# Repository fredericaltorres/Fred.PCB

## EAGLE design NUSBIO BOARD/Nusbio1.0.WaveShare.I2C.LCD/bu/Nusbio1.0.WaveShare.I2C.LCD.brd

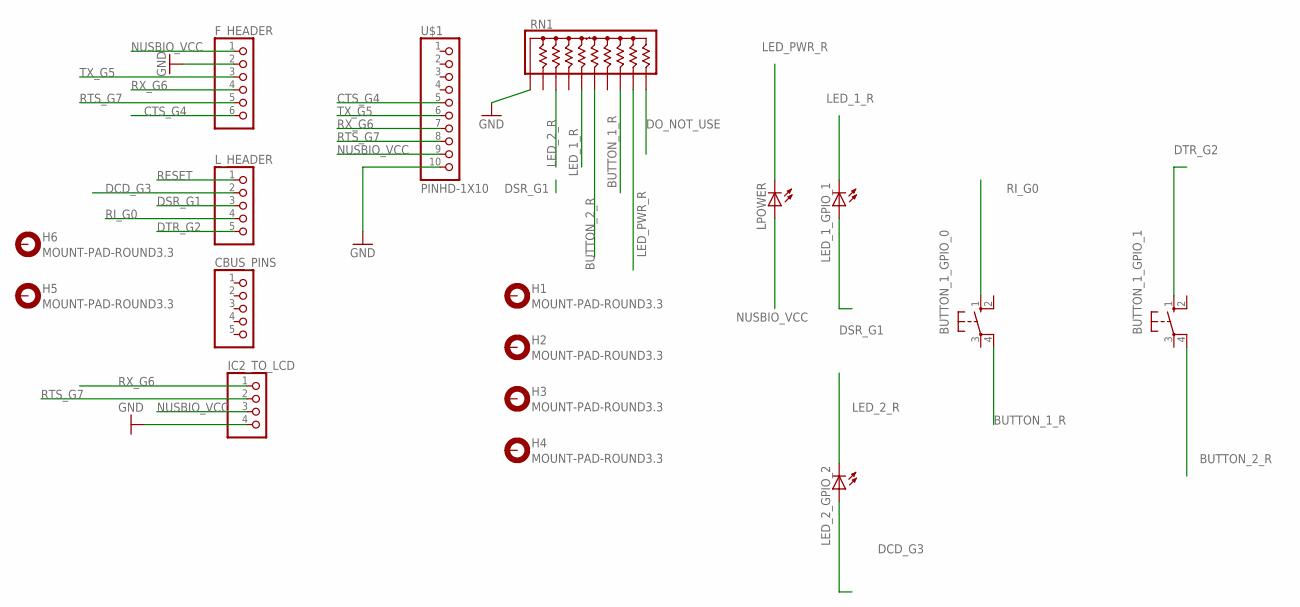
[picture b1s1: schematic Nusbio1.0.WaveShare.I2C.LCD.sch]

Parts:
BUTTON_1_GPIO_0, BUTTON_1_GPIO_1: 10-XX; B3F-10XX
CBUS_PINS: PINHD-1X5; 1X05
F_HEADER: PINHD-1X6; 1X06
H1, H2, H3, H4, H5, H6: MOUNT-PAD-ROUND3.3; 3,3-PAD
IC2_TO_LCD: PINHD-1X4; 1X04
LED_1_GPIO_1, LED_2_GPIO_2: LEDSMT1206; 1206
LPOWER: LEDSMT1206; 1206
L_HEADER: PINHD-1X5; 1X05
RN1: 4610X; SIP10
U$1: PINHD-1X10; 1X10-BIG

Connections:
BUTTON_1_R: BUTTON_1_GPIO_0.4 (P1), RN1.8
BUTTON_2_R: BUTTON_1_GPIO_1.4 (P1), RN1.6
CTS_G4: F_HEADER.6, U$1.5
DCD_G3: LED_2_GPIO_2.A, L_HEADER.2
DO_NOT_USE: RN1.10
DSR_G1: LED_1_GPIO_1.A, L_HEADER.3
DTR_G2: BUTTON_1_GPIO_1.1 (S), L_HEADER.5
GND: F_HEADER.2, IC2_TO_LCD.4, RN1.1, U$1.10
LED_1_R: LED_1_GPIO_1.C, RN1.5
LED_2_R: LED_2_GPIO_2.C, RN1.3
LED_PWR_R: LPOWER.C, RN1.9
NUSBIO_VCC: F_HEADER.1, IC2_TO_LCD.3, LPOWER.A, U$1.9
RESET: L_HEADER.1
RI_G0: BUTTON_1_GPIO_0.1 (S), L_HEADER.4
RTS_G7: F_HEADER.5, IC2_TO_LCD.2, U$1.8
RX_G6: F_HEADER.4, IC2_TO_LCD.1, U$1.7
TX_G5: F_HEADER.3, U$1.6

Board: 2 copper layers, 17 parts (0 on the bottom side), 15 nets, no tracks yet.

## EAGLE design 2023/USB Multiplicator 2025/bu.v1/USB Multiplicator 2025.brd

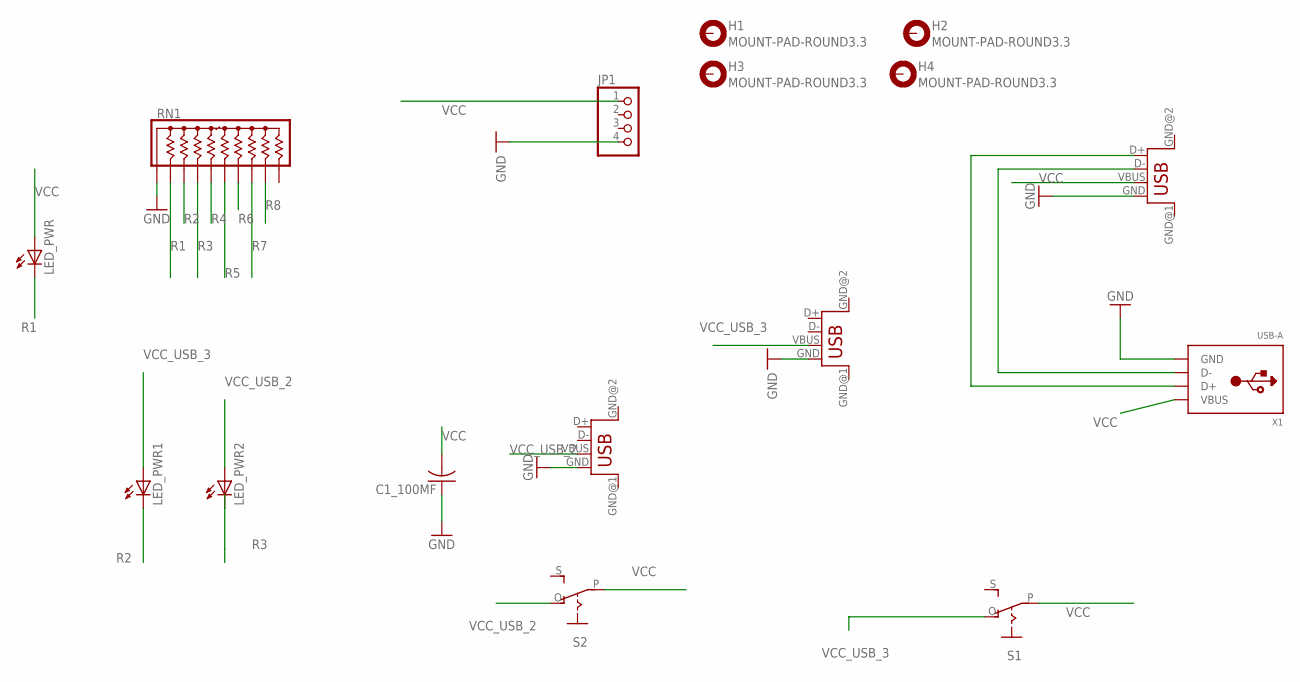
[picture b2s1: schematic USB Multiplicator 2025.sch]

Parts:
C1_100MF: C-US025-030X050; C025-030X050
H1, H2, H3, H4: MOUNT-PAD-ROUND3.3; 3,3-PAD
JP1: PINHD-1X4; 1X04
LED_PWR, LED_PWR1, LED_PWR2: LEDSMT1206; 1206
RN1: 4610X; SIP10
S1, S2: EG1218S; EG1218
USB_OUT_1, USB_OUT_2: USB; USB-FEMALE-A-PTH
USB_OUT_WITH_DATA_1: USB; USB-FEMALE-A-PTH
X1: USB-A; MOLEX_480371000

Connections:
GND: C1_100MF.1, JP1.4, RN1.1, USB_OUT_1.GND, USB_OUT_2.GND, USB_OUT_WITH_DATA_1.GND, X1.4 (GND)
unnamed: USB_OUT_WITH_DATA_1.D-, X1.2 (D-)
unnamed: USB_OUT_WITH_DATA_1.D+, X1.3 (D+)
R1: LED_PWR.C, RN1.2
R2: LED_PWR1.C, RN1.3
R3: LED_PWR2.C, RN1.4
R4: RN1.5
R5: RN1.6
R6: RN1.7
R7: RN1.8
R8: RN1.9
VCC: C1_100MF.2, JP1.1, LED_PWR.A, S1.P, S2.P, USB_OUT_WITH_DATA_1.VBUS, X1.1 (VBUS)
VCC_USB_2: LED_PWR2.A, S2.O, USB_OUT_2.VBUS
VCC_USB_3: LED_PWR1.A, S1.O, USB_OUT_1.VBUS

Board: 2 copper layers, 16 parts (0 on the bottom side), 9 nets, no tracks yet.

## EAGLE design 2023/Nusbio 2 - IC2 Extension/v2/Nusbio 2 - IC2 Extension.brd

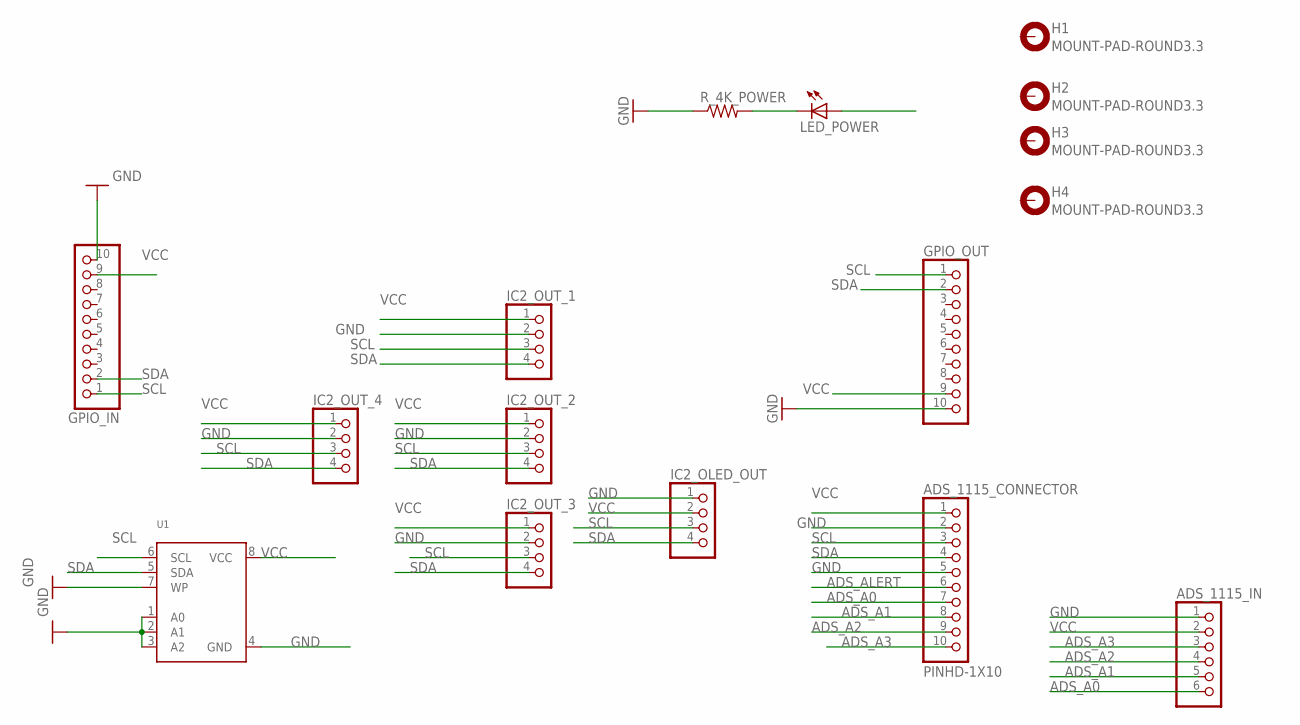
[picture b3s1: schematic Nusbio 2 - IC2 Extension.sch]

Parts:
ADS_1115_CONNECTOR: PINHD-1X10; 1X10-BIG
ADS_1115_IN: PINHD-1X6; 1X06
GPIO_IN: PINHD-1X10; 1X10-BIG
GPIO_OUT: PINHD-1X10; 1X10-BIG
H1, H2, H3, H4: MOUNT-PAD-ROUND3.3; 3,3-PAD
IC2_OLED_OUT, IC2_OUT_1, IC2_OUT_2, IC2_OUT_3, IC2_OUT_4: PINHD-1X4; 1X04
LED_POWER: LEDSMT1206; 1206
R_4K_POWER: R-US_R1206; R1206
U1: EEPROM_I2C_SOIC8_GENERIC; SOIC8_150MIL

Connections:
ADS_A0: ADS_1115_CONNECTOR.7, ADS_1115_IN.6
ADS_A1: ADS_1115_CONNECTOR.8, ADS_1115_IN.5
ADS_A2: ADS_1115_CONNECTOR.9, ADS_1115_IN.4
ADS_A3: ADS_1115_CONNECTOR.10, ADS_1115_IN.3
ADS_ALERT: ADS_1115_CONNECTOR.6
GND: ADS_1115_CONNECTOR.2, ADS_1115_CONNECTOR.5, ADS_1115_IN.1, GPIO_IN.10, GPIO_OUT.10, IC2_OLED_OUT.1, IC2_OUT_1.2, IC2_OUT_2.2, IC2_OUT_3.2, IC2_OUT_4.2, R_4K_POWER.1, U1.1 (A0), U1.2 (A1), U1.3 (A2), U1.4 (GND), U1.7 (WP)
unnamed: LED_POWER.C, R_4K_POWER.2
SCL: ADS_1115_CONNECTOR.3, GPIO_IN.1, GPIO_OUT.1, IC2_OLED_OUT.3, IC2_OUT_1.3, IC2_OUT_2.3, IC2_OUT_3.3, IC2_OUT_4.3, U1.6 (SCL)
SDA: ADS_1115_CONNECTOR.4, GPIO_IN.2, GPIO_OUT.2, IC2_OLED_OUT.4, IC2_OUT_1.4, IC2_OUT_2.4, IC2_OUT_3.4, IC2_OUT_4.4, U1.5 (SDA)
VCC: ADS_1115_CONNECTOR.1, ADS_1115_IN.2, GPIO_IN.9, GPIO_OUT.9, IC2_OLED_OUT.2, IC2_OUT_1.1, IC2_OUT_2.1, IC2_OUT_3.1, IC2_OUT_4.1, LED_POWER.A, U1.8 (VCC)

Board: 2 copper layers, 16 parts (0 on the bottom side), 9 nets, no tracks yet.

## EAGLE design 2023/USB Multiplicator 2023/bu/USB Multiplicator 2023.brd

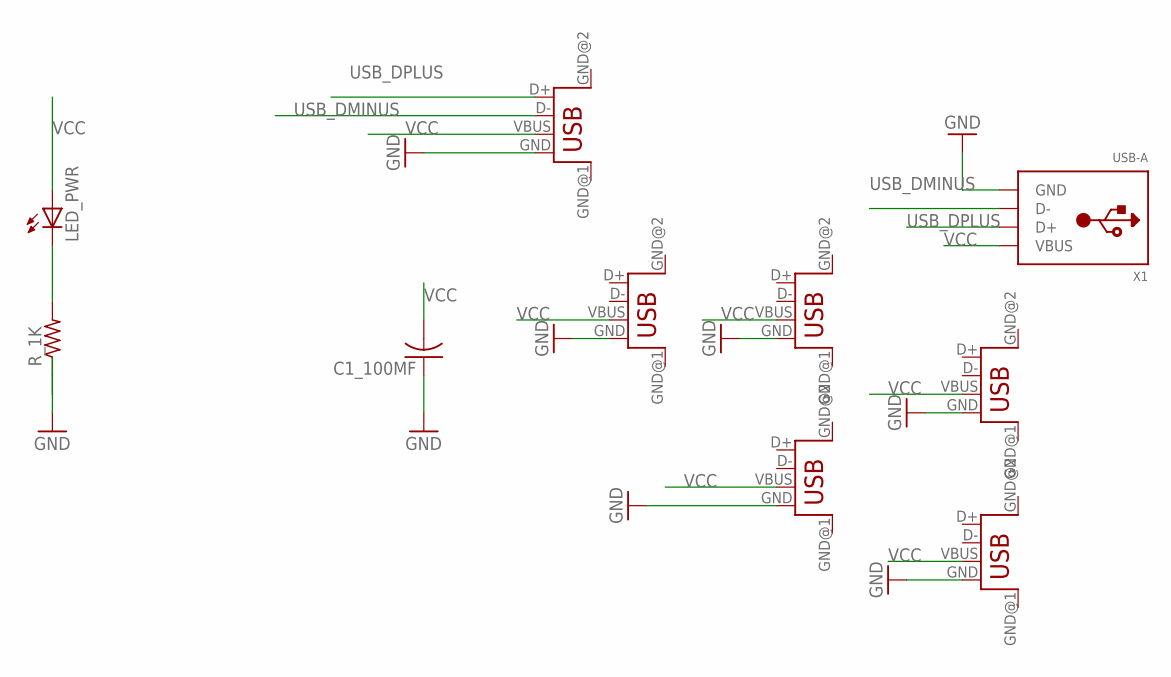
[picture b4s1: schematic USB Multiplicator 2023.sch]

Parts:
C1_100MF: C-US025-030X050; C025-030X050
LED_PWR: LEDSMT1206; 1206
R_1K: R-US_R1206; R1206
USB_OUT_2, USB_OUT_3, USB_OUT_4, USB_OUT_5, USB_OUT_6: USB; USB-FEMALE-A-PTH
USB_OUT_WITH_DATA_1: USB; USB-FEMALE-A-PTH
X1: USB-A; MOLEX_480371000

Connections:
GND: C1_100MF.1, R_1K.1, USB_OUT_2.GND, USB_OUT_3.GND, USB_OUT_4.GND, USB_OUT_5.GND, USB_OUT_6.GND, USB_OUT_WITH_DATA_1.GND, X1.4 (GND)
unnamed: LED_PWR.C, R_1K.2
USB_DMINUS: USB_OUT_WITH_DATA_1.D-, X1.2 (D-)
USB_DPLUS: USB_OUT_WITH_DATA_1.D+, X1.3 (D+)
VCC: C1_100MF.2, LED_PWR.A, USB_OUT_2.VBUS, USB_OUT_3.VBUS, USB_OUT_4.VBUS, USB_OUT_5.VBUS, USB_OUT_6.VBUS, USB_OUT_WITH_DATA_1.VBUS, X1.1 (VBUS)

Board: 2 copper layers, 10 parts (0 on the bottom side), 5 nets, no tracks yet.

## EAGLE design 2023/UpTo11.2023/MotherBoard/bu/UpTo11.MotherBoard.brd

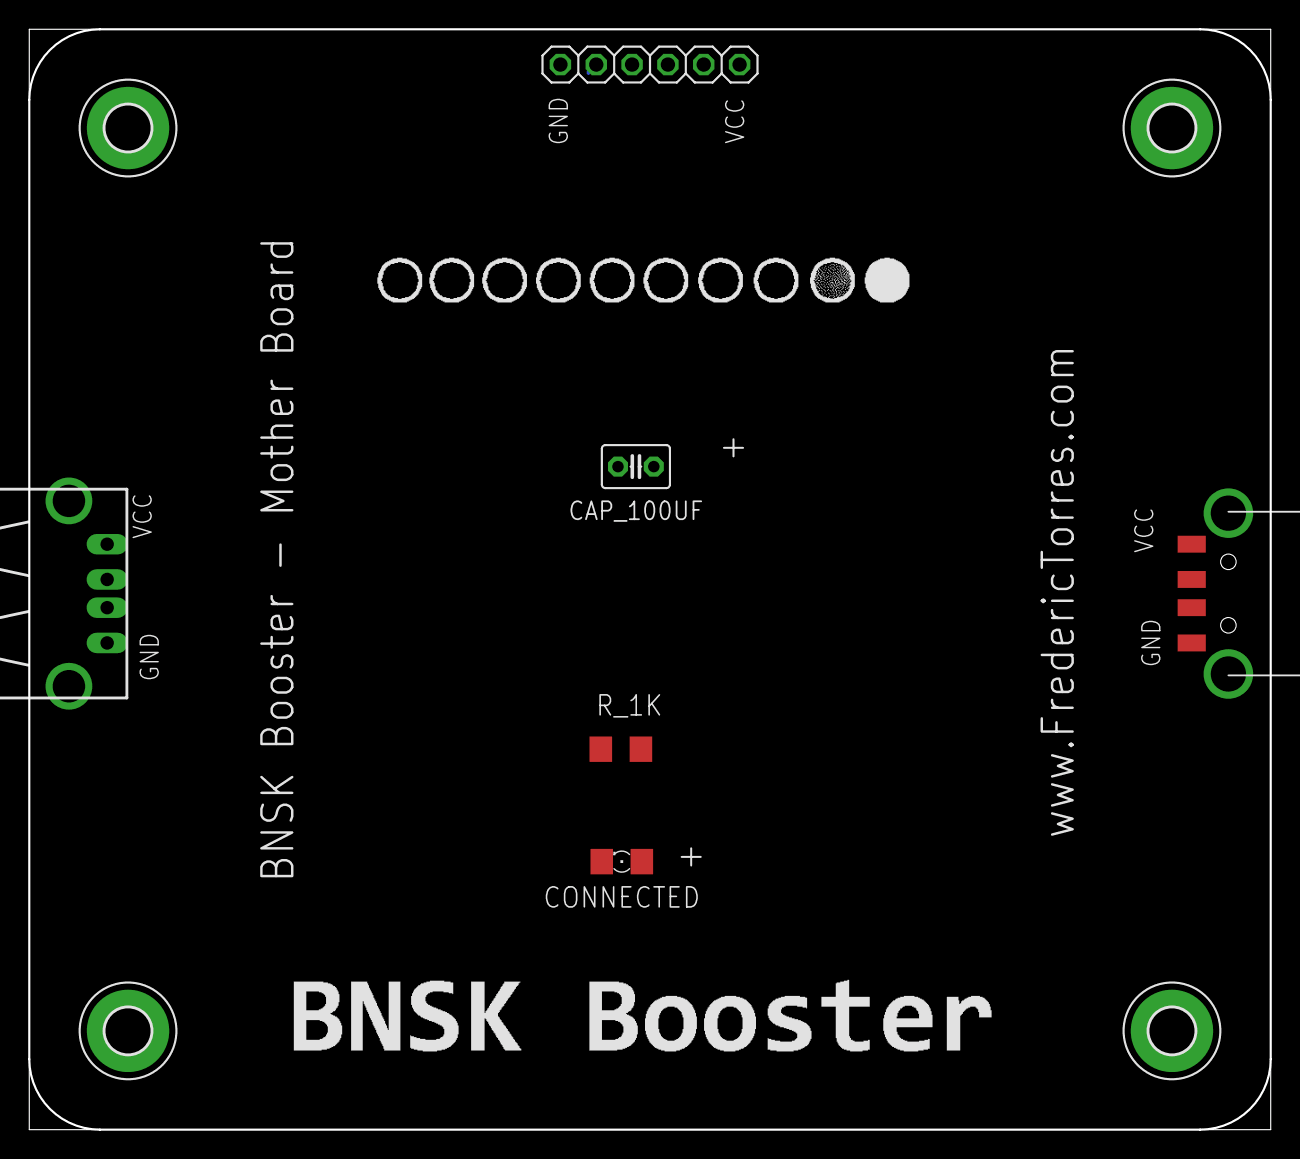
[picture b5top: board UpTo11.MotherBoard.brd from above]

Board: 2 copper layers, 88.0 x 78.0 mm, 10 parts (0 on the bottom side), 5 nets.

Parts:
CAP_100UF: C025-030X050
CN1: USB_HOST-PTH
CONNECTED: 1206
FRONT_PANEL_INTERFACE: 1X06
H1, H2, H3, H4: MOUNT-PAD-ROUND3.3; 3,3-PAD
R_1K: R1206
X1: USB-A; MOLEX_480371000

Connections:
DMINUS: CN1.D-, X1.2
DPLUS: CN1.D+, X1.3
GND_EX: CAP_100UF.1, CN1.GND, CONNECTED.C, FRONT_PANEL_INTERFACE.1, X1.4
unnamed: CONNECTED.A, R_1K.1
VCC: CAP_100UF.2, CN1.VBUS, FRONT_PANEL_INTERFACE.6, R_1K.2, X1.1

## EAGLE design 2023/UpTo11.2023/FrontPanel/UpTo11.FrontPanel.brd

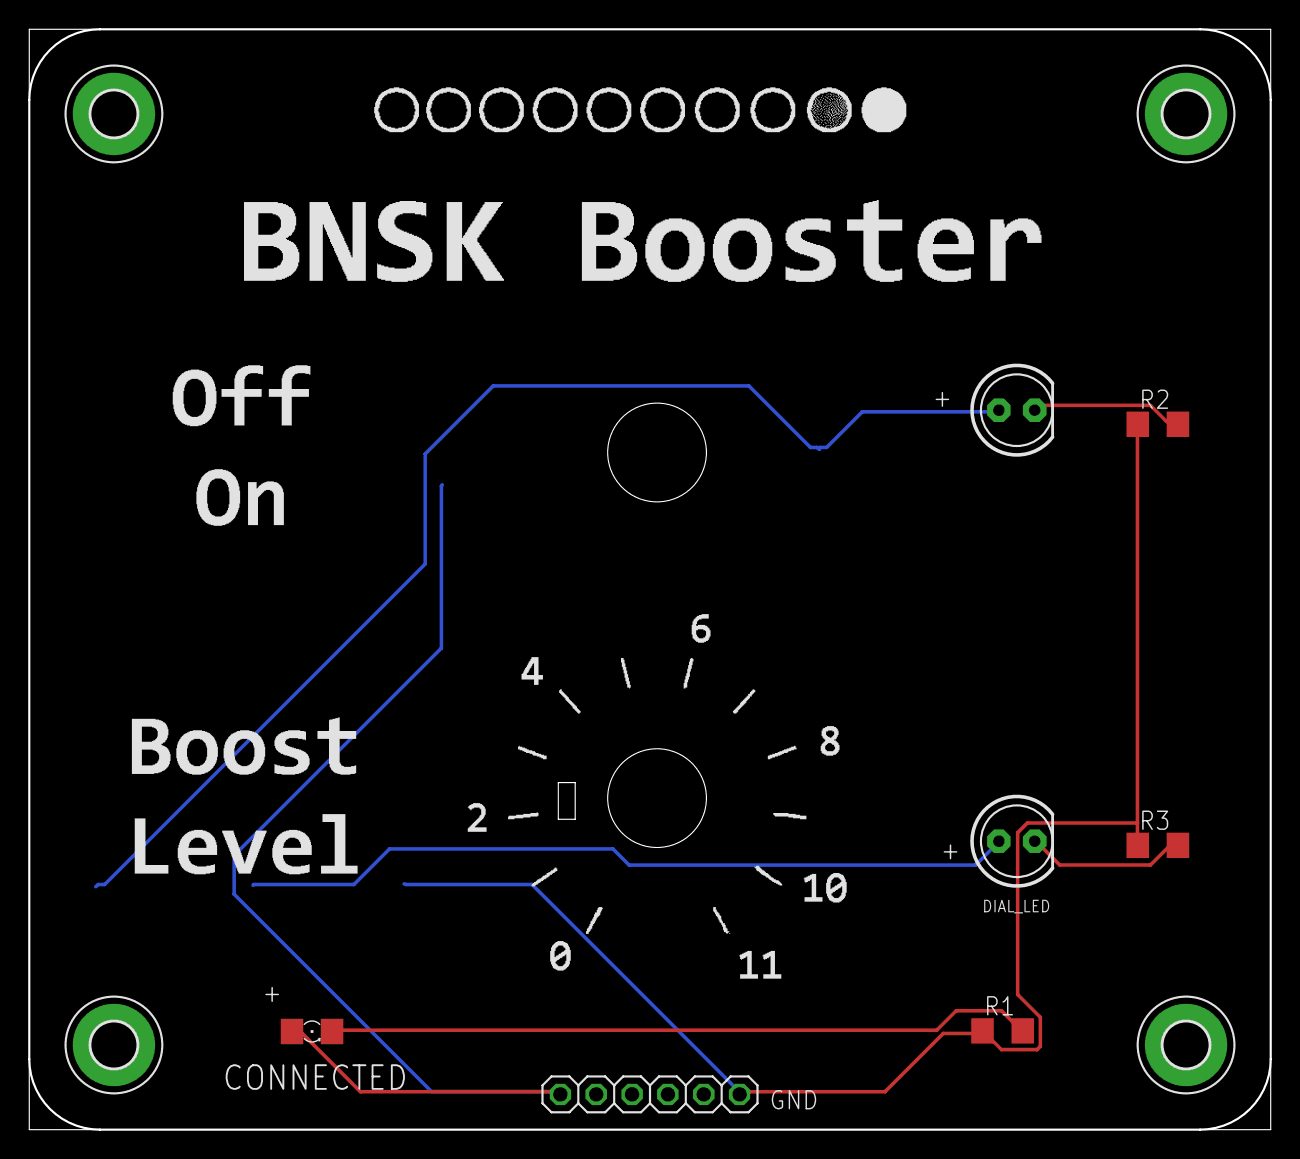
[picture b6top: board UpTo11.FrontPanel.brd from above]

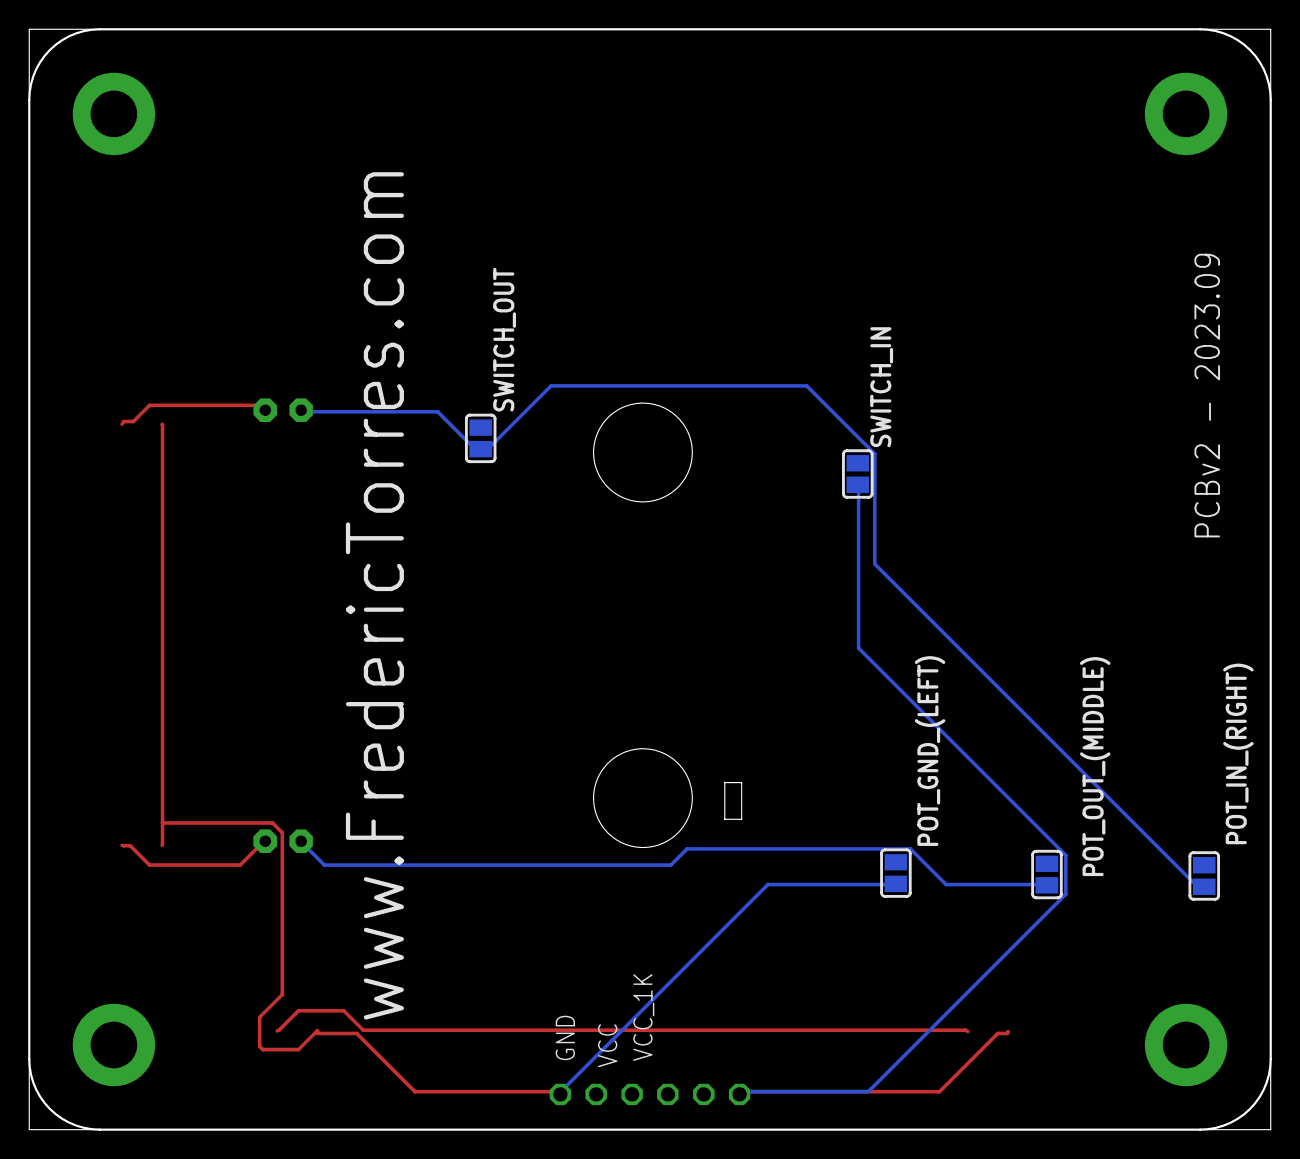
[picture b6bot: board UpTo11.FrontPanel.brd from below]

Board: 2 copper layers, 88.0 x 78.0 mm, 16 parts (5 on the bottom side), 7 nets.

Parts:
BOOSTER_ON_LED: LED5MM
CONNECTED: 1206
DIAL_LED: LED5MM
FRONT_PANEL_INTERFACE: 1X06
H1, H2, H3, H4: MOUNT-PAD-ROUND3.3; 3,3-PAD
POT_GND_(LEFT): SOLDERJUMPER_REFLOW
POT_IN_(RIGHT): SOLDERJUMPER_REFLOW
POT_OUT_(MIDDLE): SOLDERJUMPER_REFLOW
R1, R2, R3: R1206
SWITCH_IN: SOLDERJUMPER_REFLOW
SWITCH_OUT: SOLDERJUMPER_REFLOW

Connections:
BOOSTER_ON: BOOSTER_ON_LED.A, POT_IN_(RIGHT).2, SWITCH_OUT.2
DIAL_INPUT: DIAL_LED.A, POT_OUT_(MIDDLE).2
GND_EX: FRONT_PANEL_INTERFACE.1, POT_GND_(LEFT).2, R1.1, R2.1, R3.1
unnamed: CONNECTED.C, R1.2
unnamed: BOOSTER_ON_LED.K, R2.2
unnamed: DIAL_LED.K, R3.2
VCC: CONNECTED.A, FRONT_PANEL_INTERFACE.6, SWITCH_IN.2

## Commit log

2022-09-18 Rename PCB repo to fred.pcb
2022-09-18 more French usb 2
2022-09-26 2022 Authoring Lights
2022-09-28 Authoring lights
2023-01-08 BSNK Rambo converters
2023-01-16 Jenkins board
2023-02-03 new ft232 board 2023
2023-02-05 Board update
2023-02-06 FT232H board added gpio leds
2023-02-07 Flasg extension
2023-02-08 USB Experimentation Board
2023-02-11 fDrive update
2023-02-13 2023.2. PCBs
2023-02-26 Board 2023 fix first bug
2023-03-04 Add pull up resistor to ft232h and i2c out 2
2023-03-06 More on FT232 board
2023-03-08 I2C Extension
2023-03-13 Nsubio /2 v2 update
2023-03-18 Fix bug in Experiment Board
2023-03-20 change to Gx for the gpios in Nusbio/2
2023-04-07 Fix Nusbio gnd pin for gpios led resitor array
2023-04-09 Added i2c mode led on nusbio /v2
2023-04-10 Nusbio /2 v3
2023-04-10 Test Esxtension
2023-04-10 SPI Extension
2023-04-27 Nusbio I2C Extension
2023-04-29 Nusbio test extension
2023-05-24 Nusbio v2 pcb and SPIExtension v 1 2023/05
2023-06-25 Finishh and send board for summer 2023 to jlpcb
2023-08-20 new bnsk automation monitoring device
2023-08-24 usb multiplicator 2023 / French USBC
2023-08-27 Upto11 2023
2023-09-05 BNSK Booster v 2
2023-09-08 UpTo11 2023 update
2023-09-10 BNSK Booster v2
2023-09-17 Fix usb female minus/plus
2023-10-03 Fix Nusbio I2Cextension with right eeprom format
2023-10-08 USB Multiplicator update v2
2023-11-08 I2C Extension Photo
2025-07-15 Update...

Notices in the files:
parts and their libraries:
DECADE-libraries20151104: Licensing: Creative Commons ShareAlike 4.0 International - https://creativecommons.org/licenses/by-sa/4.0
microbuilder: This work is placed in the public domain, and may be freely used for commercial and non-commercial work with the following conditions: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
